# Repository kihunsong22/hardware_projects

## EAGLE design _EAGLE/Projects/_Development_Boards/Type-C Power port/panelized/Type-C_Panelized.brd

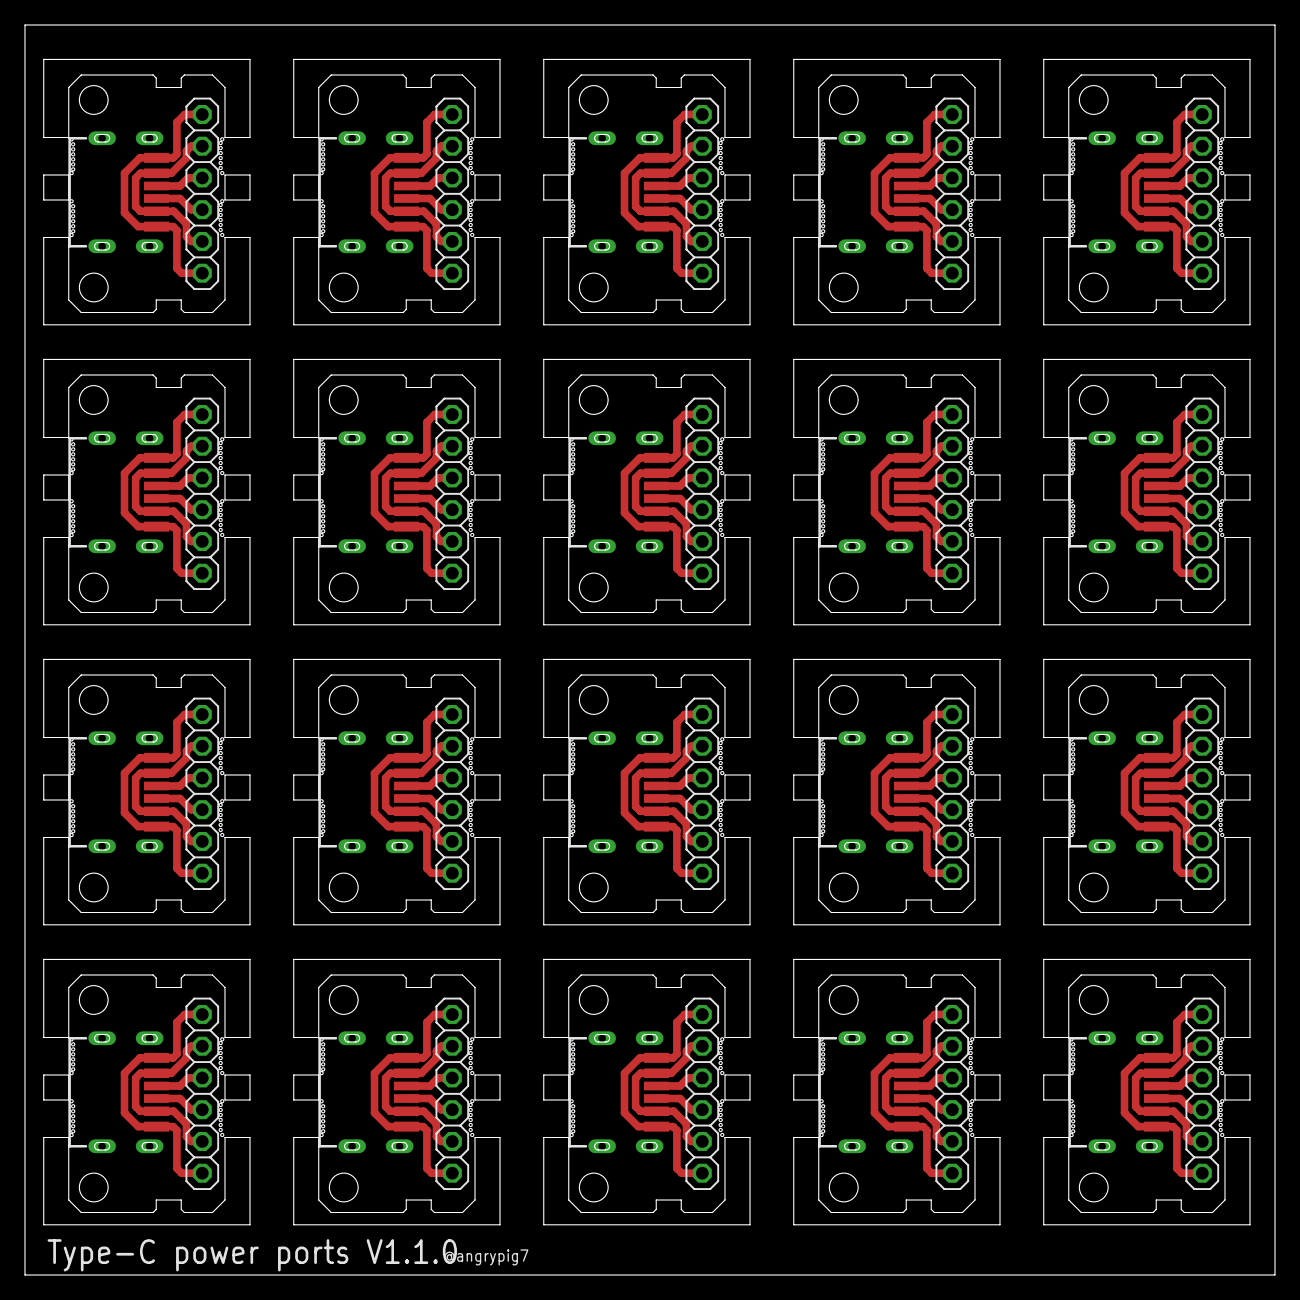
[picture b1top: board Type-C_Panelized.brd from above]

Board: 2 copper layers, 100.0 x 100.0 mm, 40 parts (0 on the bottom side), 80 nets.

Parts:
J1, J2, J3, J4, J5, J6, J7, J8, J9, J10, J11, J12, J13, J14, J15, J16, J17, J18, J19, J20: TYPE-C-31-M-17
JP1, JP2, JP3, JP4, JP5, JP6, JP7, JP8, JP9, JP10, JP11, JP12, JP13, JP14, JP15, JP16, JP17, JP18, JP19, JP20: 1X06/OCT

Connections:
unnamed: J1.VBUS, J1.VBUS_2, JP1.2, JP1.5
unnamed: J1.GND, J1.GND_2, JP1.1, JP1.6
unnamed: J1.CC1, JP1.4
unnamed: J1.CC2, JP1.3
unnamed: J2.VBUS, J2.VBUS_2, JP2.2, JP2.5
unnamed: J2.GND, J2.GND_2, JP2.1, JP2.6
unnamed: J2.CC1, JP2.4
unnamed: J2.CC2, JP2.3
unnamed: J3.VBUS, J3.VBUS_2, JP3.2, JP3.5
unnamed: J3.GND, J3.GND_2, JP3.1, JP3.6
unnamed: J3.CC1, JP3.4
unnamed: J3.CC2, JP3.3
unnamed: J4.VBUS, J4.VBUS_2, JP4.2, JP4.5
unnamed: J4.GND, J4.GND_2, JP4.1, JP4.6
unnamed: J4.CC1, JP4.4
unnamed: J4.CC2, JP4.3
unnamed: J5.VBUS, J5.VBUS_2, JP5.2, JP5.5
unnamed: J5.GND, J5.GND_2, JP5.1, JP5.6
unnamed: J5.CC1, JP5.4
unnamed: J5.CC2, JP5.3
unnamed: J6.VBUS, J6.VBUS_2, JP6.2, JP6.5
unnamed: J6.GND, J6.GND_2, JP6.1, JP6.6
unnamed: J6.CC1, JP6.4
unnamed: J6.CC2, JP6.3
unnamed: J7.VBUS, J7.VBUS_2, JP7.2, JP7.5
unnamed: J7.GND, J7.GND_2, JP7.1, JP7.6
unnamed: J7.CC1, JP7.4
unnamed: J7.CC2, JP7.3
unnamed: J8.VBUS, J8.VBUS_2, JP8.2, JP8.5
unnamed: J8.GND, J8.GND_2, JP8.1, JP8.6
unnamed: J8.CC1, JP8.4
unnamed: J8.CC2, JP8.3
unnamed: J9.VBUS, J9.VBUS_2, JP9.2, JP9.5
unnamed: J9.GND, J9.GND_2, JP9.1, JP9.6
unnamed: J9.CC1, JP9.4
unnamed: J9.CC2, JP9.3
unnamed: J10.VBUS, J10.VBUS_2, JP10.2, JP10.5
unnamed: J10.GND, J10.GND_2, JP10.1, JP10.6
unnamed: J10.CC1, JP10.4
unnamed: J10.CC2, JP10.3
unnamed: J11.VBUS, J11.VBUS_2, JP11.2, JP11.5
unnamed: J11.GND, J11.GND_2, JP11.1, JP11.6
unnamed: J11.CC1, JP11.4
unnamed: J11.CC2, JP11.3
unnamed: J12.VBUS, J12.VBUS_2, JP12.2, JP12.5
unnamed: J12.GND, J12.GND_2, JP12.1, JP12.6
unnamed: J12.CC1, JP12.4
unnamed: J12.CC2, JP12.3
unnamed: J13.VBUS, J13.VBUS_2, JP13.2, JP13.5
unnamed: J13.GND, J13.GND_2, JP13.1, JP13.6
unnamed: J13.CC1, JP13.4
unnamed: J13.CC2, JP13.3
unnamed: J14.VBUS, J14.VBUS_2, JP14.2, JP14.5
unnamed: J14.GND, J14.GND_2, JP14.1, JP14.6
unnamed: J14.CC1, JP14.4
unnamed: J14.CC2, JP14.3
unnamed: J15.VBUS, J15.VBUS_2, JP15.2, JP15.5
unnamed: J15.GND, J15.GND_2, JP15.1, JP15.6
unnamed: J15.CC1, JP15.4
unnamed: J15.CC2, JP15.3
unnamed: J16.VBUS, J16.VBUS_2, JP16.2, JP16.5
unnamed: J16.GND, J16.GND_2, JP16.1, JP16.6
unnamed: J16.CC1, JP16.4
unnamed: J16.CC2, JP16.3
unnamed: J17.VBUS, J17.VBUS_2, JP17.2, JP17.5
unnamed: J17.GND, J17.GND_2, JP17.1, JP17.6
unnamed: J17.CC1, JP17.4
unnamed: J17.CC2, JP17.3
unnamed: J18.VBUS, J18.VBUS_2, JP18.2, JP18.5
unnamed: J18.GND, J18.GND_2, JP18.1, JP18.6
unnamed: J18.CC1, JP18.4
unnamed: J18.CC2, JP18.3
unnamed: J19.VBUS, J19.VBUS_2, JP19.2, JP19.5
unnamed: J19.GND, J19.GND_2, JP19.1, JP19.6
unnamed: J19.CC1, JP19.4
unnamed: J19.CC2, JP19.3
unnamed: J20.VBUS, J20.VBUS_2, JP20.2, JP20.5
unnamed: J20.GND, J20.GND_2, JP20.1, JP20.6
unnamed: J20.CC1, JP20.4
unnamed: J20.CC2, JP20.3

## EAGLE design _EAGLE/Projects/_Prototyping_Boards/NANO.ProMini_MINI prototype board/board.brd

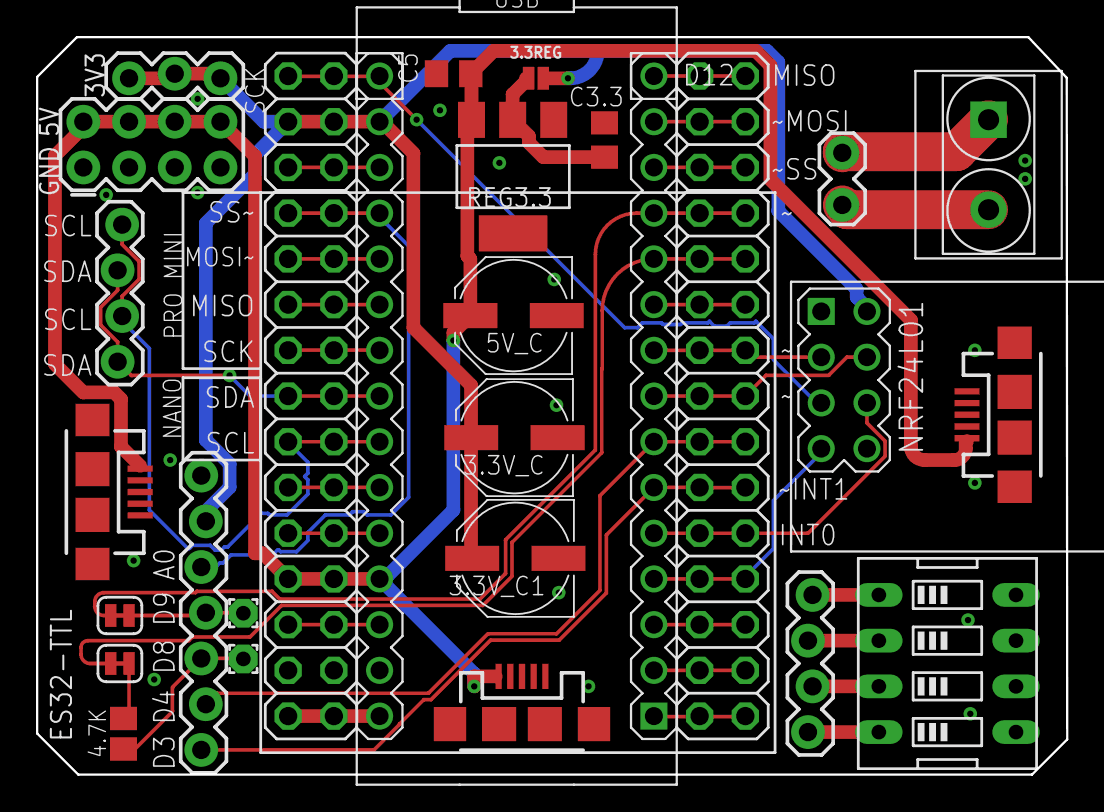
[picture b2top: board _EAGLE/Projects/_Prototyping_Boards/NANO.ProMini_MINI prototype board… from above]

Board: 2 copper layers, 57.2 x 41.0 mm, 27 parts (0 on the bottom side), 40 nets.

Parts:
3.3REG: JUMPER-SMT_2_NO_NO-SILK; SMT-JUMPER_2_NO_NO-SILK
3.3V_C, 3.3V_C1, 5V_C: PANASONIC_D
3V3: 1X03_LOCK
5.GND: 2X4
C3.3, C5: 100nF; C0805
ES32-TTL: 1X07_LOCK
I2C_1: 1X04_LOCK
J4: 1X04_LOCK
JP1, JP2: SMT-JUMPER_2_NC_TRACE_SILK
MICRO_1, MICRO_2, MICRO_3: USB-MICROB
NANO: ARDUINO-NANO-3.0
NRF24L01: WIRELESS-NRF24L01
PAD1, PAD2: 1,6/0,8
PH1, PH2: 2X15
PIN1: 1X02_LOCK
R1: 4.7k; R2012
REG3.3: REG1117; SOT223
SW1: EDG-04
T1_5MM: 5mm; H2-5.0-10.5X8.0MM

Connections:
3.3V: 3.3REG.2, 3.3V_C.+, 3.3V_C1.+, 3V3.1, 3V3.2, 3V3.3, ES32-TTL.6, NANO.J2.14, NRF24L01.2, PH1.3, PH1.4
5V: 5.GND.2, 5.GND.4, 5.GND.6, 5.GND.8, 5V_C.+, C5.1, MICRO_1.VBUS, MICRO_2.VBUS, MICRO_3.VBUS, NANO.J2.4, PH1.23, PH1.24, REG3.3.3
A6: NANO.J2.6, PH1.19, PH1.20
A7: NANO.J2.5, PH1.21, PH1.22
CE_NRF: NANO.J1.9, NRF24L01.3, PH2.13, PH2.14
CSN_NRF: NANO.J1.8, NRF24L01.4, PH2.15, PH2.16
ES32_AUX: ES32-TTL.5, NANO.J2.12, PH1.7, PH1.8
ES32_RXD: ES32-TTL.3, PAD2.1, R1.2
ES32_TXD: JP2.1, NANO.J1.12, PH2.7, PH2.8
GND: 3.3V_C.-, 3.3V_C1.-, 5.GND.1, 5.GND.3, 5.GND.5, 5.GND.7, 5V_C.-, C3.3.1, C5.2, ES32-TTL.7, MICRO_1.GND, MICRO_2.GND, MICRO_3.GND, NANO.J2.2, NRF24L01.1, PH1.27, PH1.28, REG3.3.1, SW1.5, SW1.6, SW1.7, SW1.8
M0: ES32-TTL.1, NANO.J1.6, PH2.19, PH2.20
M1: ES32-TTL.2, NANO.J1.7, PH2.17, PH2.18
MISO_NRF: NANO.J1.4, NRF24L01.7, PH2.23, PH2.24
MOSI_NRF: NANO.J1.5, NRF24L01.6, PH2.21, PH2.22
unnamed: NANO.J1.14, PH2.3, PH2.4
unnamed: 3.3REG.1, C3.3.2, REG3.3.2
unnamed: NANO.J2.13, PH1.5, PH1.6
unnamed: NANO.J1.13, PH2.5, PH2.6
unnamed: NANO.J2.11, PH1.9, PH1.10
unnamed: NANO.J2.10, PH1.11, PH1.12
unnamed: NANO.J2.9, PH1.13, PH1.14
unnamed: JP1.2, R1.1
unnamed: ES32-TTL.4, JP2.2, PAD1.1
unnamed: NANO.J1.15, PH2.1, PH2.2
unnamed: JP1.1, NANO.J1.11, PH2.9, PH2.10
unnamed: NANO.J1.10, PH2.11, PH2.12
unnamed: PIN1.2, T1_5MM.1
unnamed: PIN1.1, T1_5MM.2
unnamed: NANO.J1.3, PH2.25, PH2.26
unnamed: NANO.J1.2, PH2.27, PH2.28
unnamed: NANO.J1.1, PH2.29, PH2.30
unnamed: J4.1, SW1.4
unnamed: J4.2, SW1.3
unnamed: J4.3, SW1.2
unnamed: J4.4, SW1.1
RST: NANO.J2.3, PH1.25, PH1.26
SCK_NRF: NANO.J2.15, NRF24L01.5, PH1.1, PH1.2
SCL: I2C_1.1, I2C_1.3, NANO.J2.7, PH1.17, PH1.18
SDA: I2C_1.2, I2C_1.4, NANO.J2.8, PH1.15, PH1.16
VIN: NANO.J2.1, PH1.29, PH1.30

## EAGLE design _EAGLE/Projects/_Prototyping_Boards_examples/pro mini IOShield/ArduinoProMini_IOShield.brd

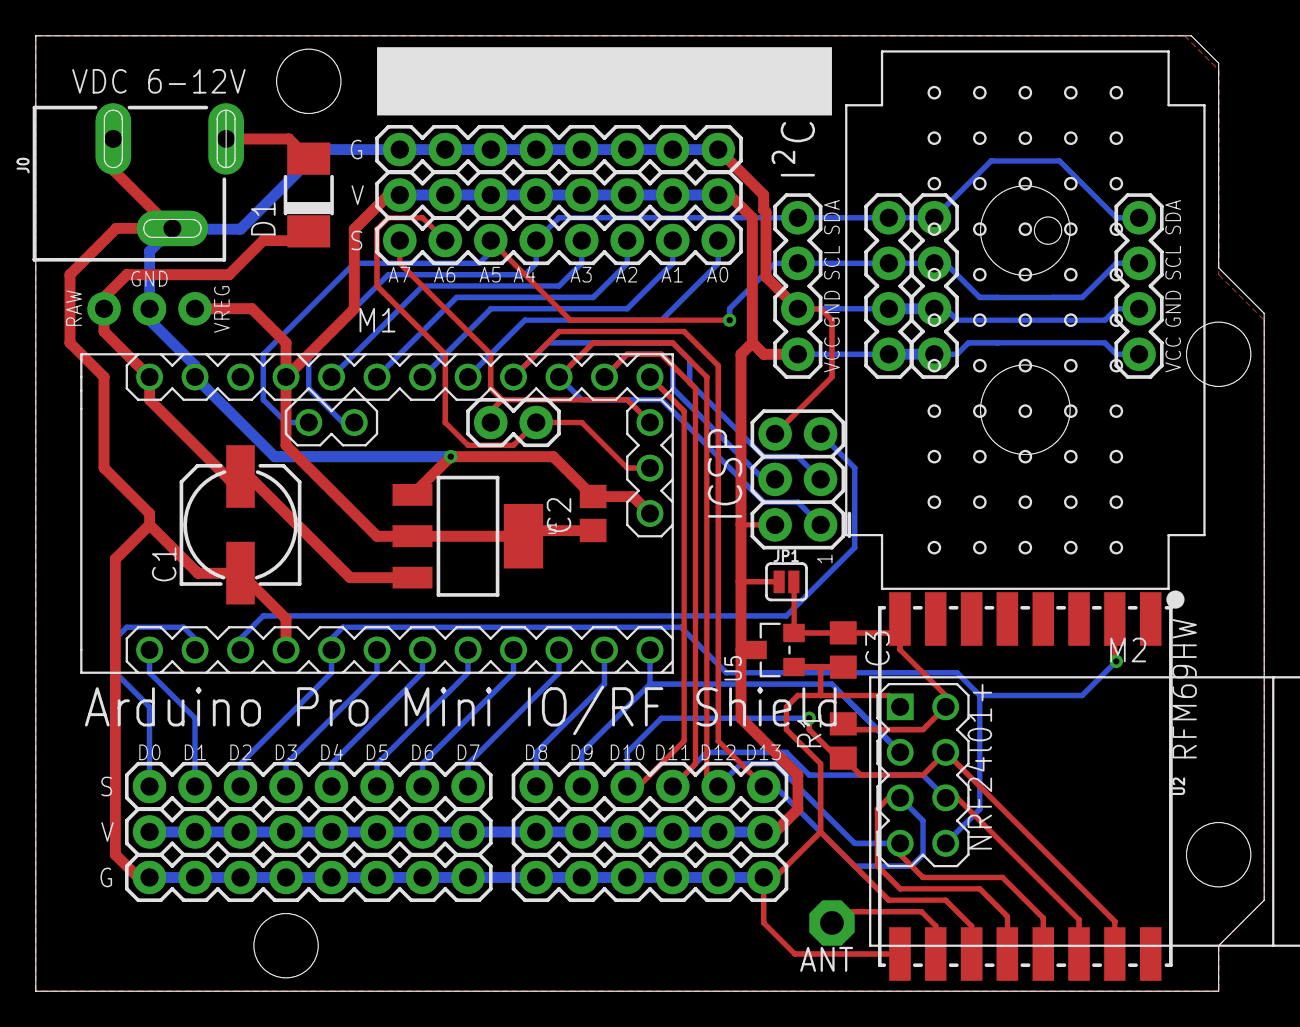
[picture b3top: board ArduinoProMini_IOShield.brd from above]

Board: 2 copper layers, 68.6 x 53.3 mm, 31 parts (0 on the bottom side), 29 nets.

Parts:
ANT: PAD-01
B1: ARDUINO_DIMENSION-DIMENSION; ARDUINOR3
C1: 10-100µF; 153CLV-0605
C2: 10-100µF; C0805
C3: 10µF; C0805
D1: M7 / 1N4007; DO-214AC
J0: POWER_JACKSLT; POWER_JACK_SLOT
J1: Analog; 1X08
J2: VCC-Analog; 1X08
J3: GND-Analog; 1X08
J4: Digital 0-7; 1X08
J5: VCC_Digital; 1X08
J6: GND-Digital; 1X08
J7: Digital 8-13; 1X06
J8: VCC-Digital; 1X06
J9: GND-Digital; 1X06
J10, J11, J12, J13: 1X04
J14: AVR_SPI_PROG_3X2PTH; 2X3
J15: orig.conn.; 1X02
J16: 1X03_NO_SILK
JP1: 3.3V No regulator; SMT-JUMPER_2_NO_SILK
M1: ARDUINO-PRO-MINI; ARDUINO-PRO-MINI#NP
M2: WIRELESS-NRF24L01
R1: R0805
U1: AMS1117-5.0; SOT223
U2: RFM69HW; RFM69W-XXXS2
U5: XC6206P332MR-G-SOT23; SOT-23
U$1: MINI_BREADBOARD; MINI_BREADBOARD_11X5

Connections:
A0: J1.1, M1.J6.8
A1: J1.2, M1.J6.7
A2: J1.3, M1.J6.6
A3: J1.4, M1.J6.5
A4: J1.5, J10.SDA, J11.SDA, J12.SDA, J13.SDA, M1.J2.1
A5: J1.6, J10.SCL, J11.SCL, J12.SCL, J13.SCL, M1.J2.2
A6: J1.7, J15.1, M1.J3.2
A7: J1.8, J15.2, M1.J3.3
D0: J4.1, M1.J7.11
D1: J4.2, M1.J7.12
D2: J4.3, M1.J7.8, M2.8, U2.2
D3: J4.4, M1.J7.7
D4: J4.5, M1.J7.6
D5: J4.6, M1.J7.5
D6: J4.7, M1.J7.4
D7: J4.8, M1.J7.3
D8: J7.1, M1.J7.2
D9: J7.2, M1.J7.1, M2.3
D10: J7.3, M1.J6.12, M2.4, R1.1, U2.15
D11: J7.4, J14.4, M1.J6.11, M2.6, U2.14
D12: J7.5, J14.1, M1.J6.10, M2.7, U2.13
D13: J7.6, J14.3, M1.J6.9, M2.5, U2.12
GND: C1.-, C2.2, C3.2, J0.GND@1, J0.GND@2, J3.1, J3.2, J3.3, J3.4, J3.5, J3.6, J3.7, J3.8, J6.1, J6.2, J6.3, J6.4, J6.5, J6.6, J6.7, J6.8, J9.1, J9.2, J9.3, J9.4, J9.5, J9.6, J10.GND, J11.GND, J12.GND, J13.GND, J14.6, J16.2, M1.J3.1, M1.J6.2, M1.J7.9, M2.1, U1.1, U2.9, U2.11, U5.1
unnamed: D1.A, J0.PWR
unnamed: ANT.1, U2.10
RAW: C1.+, D1.C, J16.1, M1.J6.1, U1.3
RST: J14.5, M1.J7.10
VCC: C2.1, J2.1, J2.2, J2.3, J2.4, J2.5, J2.6, J2.7, J2.8, J5.1, J5.2, J5.3, J5.4, J5.5, J5.6, J5.7, J5.8, J8.1, J8.2, J8.3, J8.4, J8.5, J8.6, J10.VCC, J11.VCC, J12.VCC, J13.VCC, J14.2, J16.3, JP1.1, M1.J6.4, U1.2, U1.4, U5.3
VCC_3.3V: C3.1, JP1.2, M2.2, R1.2, U2.8, U5.2

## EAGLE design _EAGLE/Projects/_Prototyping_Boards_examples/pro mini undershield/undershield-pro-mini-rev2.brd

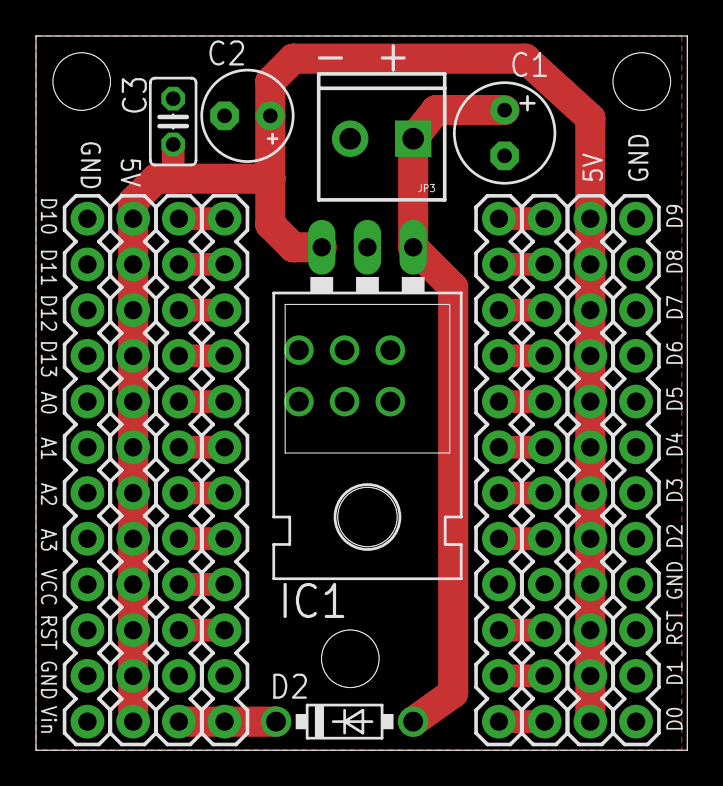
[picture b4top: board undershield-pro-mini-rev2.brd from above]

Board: 2 copper layers, 36.2 x 39.7 mm, 14 parts (0 on the bottom side), 25 nets.

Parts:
.5V, .5V1, .GND, .GND1: M12PTH; 1X12
C1: E2,5-6
C2: E2,5-5
C3: C025-025X050
D2: 1N5817-B; DO41-7.6
IC1: TO-220-ALT
JP3: SCREWTERMINAL-3.5MM-2
JPLEFT: M12PTH; 1X12
JPNANOL: M12PTH; 1X12
JPNANOR: M12PTH; 1X12
JPRIGHT: M12PTH; 1X12

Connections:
1: C1.+, D2.A, IC1.IN, JP3.1
5V: .5V.1, .5V.2, .5V.3, .5V.4, .5V.5, .5V.6, .5V.7, .5V.8, .5V.9, .5V.10, .5V.11, .5V.12, .5V1.1, .5V1.2, .5V1.3, .5V1.4, .5V1.5, .5V1.6, .5V1.7, .5V1.8, .5V1.9, .5V1.10, .5V1.11, .5V1.12, C2.+, C3.1, IC1.OUT
GND: .GND.1, .GND.2, .GND.3, .GND.4, .GND.5, .GND.6, .GND.7, .GND.8, .GND.9, .GND.10, .GND.11, .GND.12, .GND1.1, .GND1.2, .GND1.3, .GND1.4, .GND1.5, .GND1.6, .GND1.7, .GND1.8, .GND1.9, .GND1.10, .GND1.11, .GND1.12, C1.-, C2.-, C3.2, IC1.GND, JP3.2, JPLEFT.2, JPNANOL.2, JPNANOR.4, JPRIGHT.4
unnamed: JPNANOR.1, JPRIGHT.1
unnamed: JPLEFT.12, JPNANOL.12
unnamed: JPLEFT.4, JPNANOL.4
unnamed: D2.C, JPLEFT.1, JPNANOL.1
unnamed: JPLEFT.3, JPNANOL.3
unnamed: JPLEFT.5, JPNANOL.5
unnamed: JPLEFT.6, JPNANOL.6
unnamed: JPLEFT.7, JPNANOL.7
unnamed: JPLEFT.8, JPNANOL.8
unnamed: JPLEFT.9, JPNANOL.9
unnamed: JPLEFT.10, JPNANOL.10
unnamed: JPLEFT.11, JPNANOL.11
unnamed: JPNANOR.2, JPRIGHT.2
unnamed: JPNANOR.3, JPRIGHT.3
unnamed: JPNANOR.5, JPRIGHT.5
unnamed: JPNANOR.6, JPRIGHT.6
unnamed: JPNANOR.7, JPRIGHT.7
unnamed: JPNANOR.8, JPRIGHT.8
unnamed: JPNANOR.9, JPRIGHT.9
unnamed: JPNANOR.10, JPRIGHT.10
unnamed: JPNANOR.11, JPRIGHT.11
unnamed: JPNANOR.12, JPRIGHT.12

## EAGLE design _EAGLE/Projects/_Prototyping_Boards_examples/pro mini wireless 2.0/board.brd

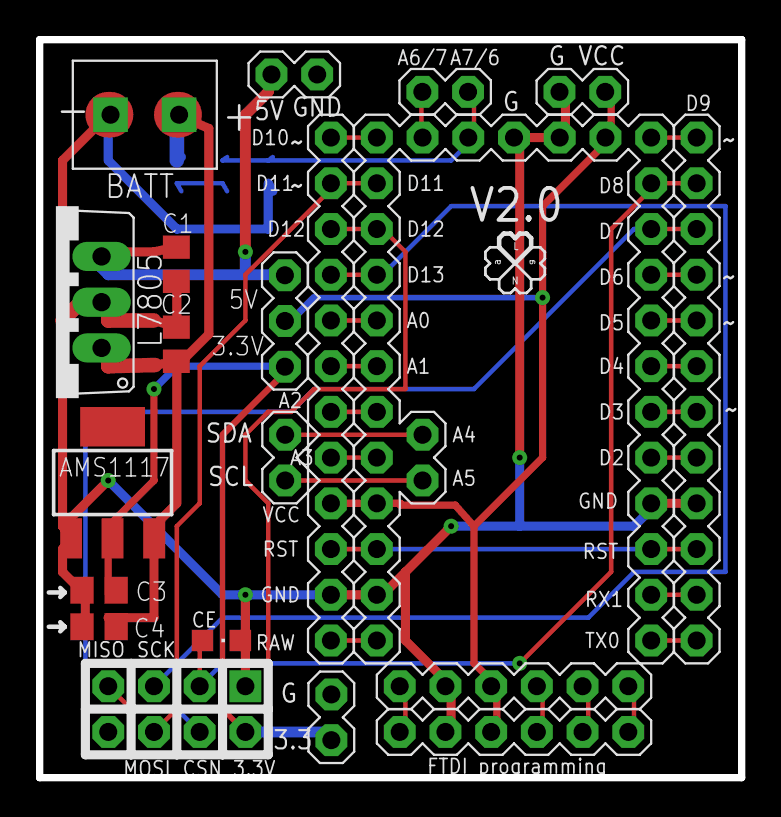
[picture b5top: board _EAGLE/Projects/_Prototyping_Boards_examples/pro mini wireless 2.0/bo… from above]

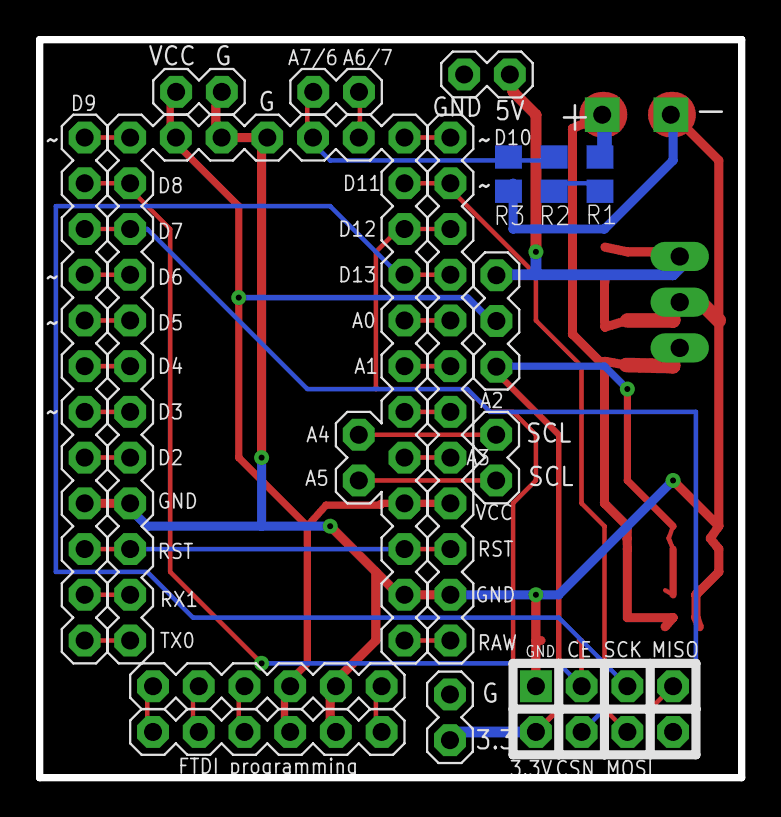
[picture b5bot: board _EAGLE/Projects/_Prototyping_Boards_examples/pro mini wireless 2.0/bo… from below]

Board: 2 copper layers, 39.0 x 41.0 mm, 18 parts (3 on the bottom side), 34 nets.

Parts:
BAT1: BLOCKTERM
IC1: 7805TV; TO220V
U$1: 6PIN
U$2: 0805_SMD_LED
U$3: AMS1117
U$4: ARDUINO
U$5: ARDUINO-PIN-BREAKOUT; ARDUINO_PIN_BREAKOUT
U$6: NRF24L01+
U$7, U$8, U$9: 0805-RESISTOR; 0805
U$10: 3PIN
U$11, U$12, U$13, U$14: 0805-CAPACITOR; 0805
U$15, U$16: 2PIN

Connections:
3.3V: U$3.2, U$6.3.3V, U$10.3, U$13.2, U$15.1
5V: IC1.3, U$10.1, U$12.2, U$16.2
BAT+: BAT1.P$1, IC1.1, U$3.3, U$7.2, U$11.1, U$14.2
CE: U$2.A, U$4.D8, U$5.11, U$6.CE
CSN: U$4.D7, U$5.10, U$6.CSN
GND: BAT1.P$2, IC1.2, U$1.5, U$2.C, U$3.1, U$4.GND, U$4.GND_1, U$4.GND_2, U$4.GND_3, U$4.GND_4, U$5.4, U$5.14, U$5.27, U$6.GND, U$9.1, U$11.2, U$12.1, U$13.1, U$14.1, U$15.2, U$16.1
MISO: U$4.D12, U$5.19, U$6.MISO
MOSI: U$4.D11, U$5.18, U$6.MOSI
unnamed: U$7.1, U$8.1
unnamed: U$4.A7/A6, U$5.15, U$8.2, U$9.2
unnamed: U$4.D9, U$5.12
unnamed: U$1.6, U$4.BLK
unnamed: U$4.A4, U$5.30
unnamed: U$4.A5, U$5.29
unnamed: U$1.3, U$4.RX
unnamed: U$1.2, U$4.TX
unnamed: U$1.1, U$4.GRN
unnamed: U$4.RAW, U$5.28
unnamed: U$4.A3, U$5.24
unnamed: U$4.A2, U$5.23
unnamed: U$4.A1, U$5.22
unnamed: U$4.A0, U$5.21
unnamed: U$4.D10, U$5.17
unnamed: U$4.A6/A7, U$5.16
unnamed: U$4.D6, U$5.9
unnamed: U$4.D5, U$5.8
unnamed: U$4.D4, U$5.7
unnamed: U$4.D3, U$5.6
unnamed: U$4.D2, U$5.5
unnamed: U$4.RX_1, U$5.2
unnamed: U$4.TX_1, U$5.1
RST: U$4.RST, U$4.RST_1, U$5.3, U$5.26
SCK: U$4.D13, U$5.20, U$6.SCK
VCC: U$1.4, U$4.3.3, U$4.3.3_1, U$4.3.3_2, U$5.13, U$5.25, U$10.2

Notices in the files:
_EAGLE/Projects/_Prototyping_Boards_examples/pro mini IOShield/ArduinoProMini_IOShield.brd:
Licensed under the CERN OHL v1.2
parts and their libraries:
SparkFun-Connectors: Licensing: Creative Commons ShareAlike 4.0 International - https://creativecommons.org/licenses/by-sa/4.0
diy-modules: Released under the Creative Commons Attribution 4.0 International License: http://creativecommons.org/licenses/by/4.0
